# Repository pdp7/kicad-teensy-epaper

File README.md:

# E-Paper Badge with Teensy LC designed in KiCad
E-Paper badge designed in [KiCad](http://kicad.org/) to connect [Pervasive Displays 2.15" E-Paper](http://www.digikey.com/product-detail/en/pervasive-displays/E2215CS062/E2215CS062-ND/5975949) to [Teensy LC](http://store.oshpark.com/products/teensy-lc). _([Teensy 3.2](https://oshpark.com/teensy) is also compatible)._  Based [Teensy E-Paper Shield](https://blog.oshpark.com/2016/08/27/teensy-e-paper-shield/) by [Jarek Lupinski](https://hackaday.io/Jarek) in EAGLE.

## OSH Park shared project
* [KiCad Teensy E-Paper Badge](https://oshpark.com/shared_projects/VzRNemk1)

## KiCad PCB design files
* repo: [kicad-teensy-epaper](https://github.com/pdp7/kicad-teensy-epaper/)
* commit: [add JST connector for lipo battery [abcafec]](https://github.com/pdp7/kicad-teensy-epaper/commit/abcafeccad423acb4cc5d59347c79b58a7b5082b)
* requires KiCad library [wickerlib](https://github.com/wickerbox/wickerlib) by [Jenner Hanni](http://jennerhanni.net/) of [Wickerbox Electronics](http://wickerbox.net/) for the 34-position FPC connector that the e-paper display plugs into:
  * [CONN-HEADER-FH34SRJ-34S-0.5SH.kicad_mod](https://github.com/wickerbox/wickerlib/blob/master/libraries/Wickerlib.pretty/CONN-HEADER-FH34SRJ-34S-0.5SH.kicad_mod)

## Bill of Materials (BoM)
* [OSH Stencils](https://www.oshstencils.com/#projects/83952319ea2abc27d46ef9cab843063dbfd85e58): stainless steel stencil
* [Teensy LC](http://store.oshpark.com/products/teensy-lc) sold by OSH Park. Designed and manufactured by [PJRC](https://www.pjrc.com/teensy/teensyLC.html).
  * _[Teensy 3.2](https://oshpark.com/teensy) is also compatible but more expensive_
* [Pervasive Displays 2.15" e-paper with ITC](http://www.pervasivedisplays.com/products/215)
  * Mfg part number: E2215CS062
  * Digi-Key: [E2215CS062-ND](http://www.digikey.com/product-detail/en/pervasive-displays/E2215CS062/E2215CS062-ND/5975949)
  * Datasheet: [2.15" TFT EPD Panel (E2215CS062)](http://www.pervasivedisplays.com/LiteratureRetrieve.aspx?ID=232067)
  * App note: [2.15" Aurora_Mb Application Note](http://www.pervasivedisplays.com/LiteratureRetrieve.aspx?ID=232068)
* [Hirose FH34SRJ-34S-0.5SH FPC connector](https://www.digikey.com/short/3hv1q0)
  * Mfg part number: FH34SRJ-34S-0.5SH(99)
  * Digi-Key: [H124726CT-ND](https://www.digikey.com/short/3hv1q0)
  * Datasheet: [FH34(S) Series Datasheet](https://www.hirose.com/product/en/download_file/key_name/FH34SRJ/category/Catalog/doc_file_id/31646/?file_category_id=4&item_id=27&is_series=1)
* [JST connector for LiPo battery](https://www.digikey.com/short/312bmm)
  * Mfg part number: S2B-PH-SM4-TB(LF)(SN)
  * Digikey: [455-1749-1-ND](https://www.digikey.com/short/312bmm) _(CONN HEADER PH SIDE 2POS 2MM SMD)_
  * Datasheet: [JST PH connector](http://www.jst-mfg.com/product/pdf/eng/ePH.pdf)  
* Teensy headers
  * Digikey: [S7012-ND](https://www.digikey.com/short/3db830) _(CONN HEADER FEMALE 14POS.1" TIN)_
  * optional as Teensy can be soldered directly to PCB
* Capacitor 1uF 0805 _(quantity 9)_
  * Digi-Key: [1276-1066-1-ND](https://www.digikey.com/short/3db8tm) _(CAP CER 1UF 25V X7R 0805)_
  * Reference: C1 C3 C4 C5 C6 C7 C8 C9 C10
  * _Note: it is cheaper to purhcase qty 10_
* Capacitor 2.2uF 0805
  * Digi-Key: [1276-2953-1-ND](https://www.digikey.com/short/3db8tp) _(CAP CER 2.2UF 25V X7R 0805)_
  * Reference: C2
* Inductor 47uH
  * Digi-Key: [732-7252-1-ND](https://www.digikey.com/short/3db8tq) _(FIXED IND 47UH 800MA 521 MOHM)_
  * Reference: L1
* Mosfet N-Ch SOT23
  * Digi-Key: [785-1012-1-ND](https://www.digikey.com/short/3db8t8) _(MOSFET N-CH 30V 3.8A SOT23)_
  * Reference: Q1
* Resistor 2.2 Ohm 0805
  * Digi-Key: [311-2.20CRCT-ND](https://www.digikey.com/short/3db8tz) _(RES SMD 2.2 OHM 1% 1/8W 0805)_
  * Reference: R1
* Schotty diodes SOD123 _(quantity 3)_
  * Digi-Key: [MBR0530CT-ND](https://www.digikey.com/short/3db883) _(DIODE SCHOTTKY 30V 500MA SOD123)_
  * Reference: D1 D2 D3

### [Digi-Key shopping cart](http://www.digikey.com/short/312b57)

### Battery Power
* **WARNING: The trace between VIN and VUSB must be cut!**
  * [Demostration of cutting the trace](https://learn.adafruit.com/assets/28069) on Adafruit Learning System.
* **[Lithium Ion Polymer Battery - 3.7v 500mAh](https://www.adafruit.com/product/1578)** from Adafruit
  * capacity chosen for a good trade off between weight and power
  * TODO: measure how long board will run with different capacities.

## Source Code
* uses [EPD215](https://github.com/jarek319/EPD215) Arduino Library by Jarek Lupinski for his E-paper Teensy Shield
* requires pinout modification:
  * example: [bringahackmfba17-dorkbotpdx.ino](https://github.com/pdp7/kicad-teensy-epaper/blob/master/firmware/bringahackmfba17-dorkbotpdx/bringahackmfba17-dorkbotpdx.ino#L6)
  * `EPD215 epaper( 17, 16, 14, 15, 13, 11 );`
 * rotation hack in [`EPD215.cpp`](https://github.com/pdp7/EPD215/commit/f4e22660877759e53a3a83ed35c6e7a54616d285#diff-a3705673e6074c2678102896fd9fc17b)
   * text and graphics wil be upside down without this
   * [quick hack to set rotation](https://github.com/pdp7/EPD215/commit/f4e22660877759e53a3a83ed35c6e7a54616d285) based on [Adafruit documentation](https://learn.adafruit.com/adafruit-gfx-graphics-library/rotating-the-display): 
   * Landscape mode:
     * `_rotation = 1`
   * Portrait mode:
     * `_rotation = 2`
   * I don't use this for the examples program that just display bitmaps as I just flip the image before generating the byte array from the bitmap file

**TODO:** library should be modified to accept rotation parameter
  
## Photos
* [Google Photos gallery](https://goo.gl/photos/csZV9jxah2BSP6vG9)
* [images directory in github repo](https://github.com/pdp7/kicad-teensy-epaper/tree/master/images)

## Video
* [YouTube: *E-Paper Badge with Teensy LC designed in KiCad*](https://www.youtube.com/watch?v=AxnLgPFTEOA)

## Related: Jarek's ePaper Teensy shield
  * OSH Park shared project: [Teensy e-Paper shield](https://oshpark.com/shared_projects/3KynIVn6)
  * My repo of Jarek's design files: [TeensyEpaperShield](https://github.com/pdp7/TeensyEpaperShield)

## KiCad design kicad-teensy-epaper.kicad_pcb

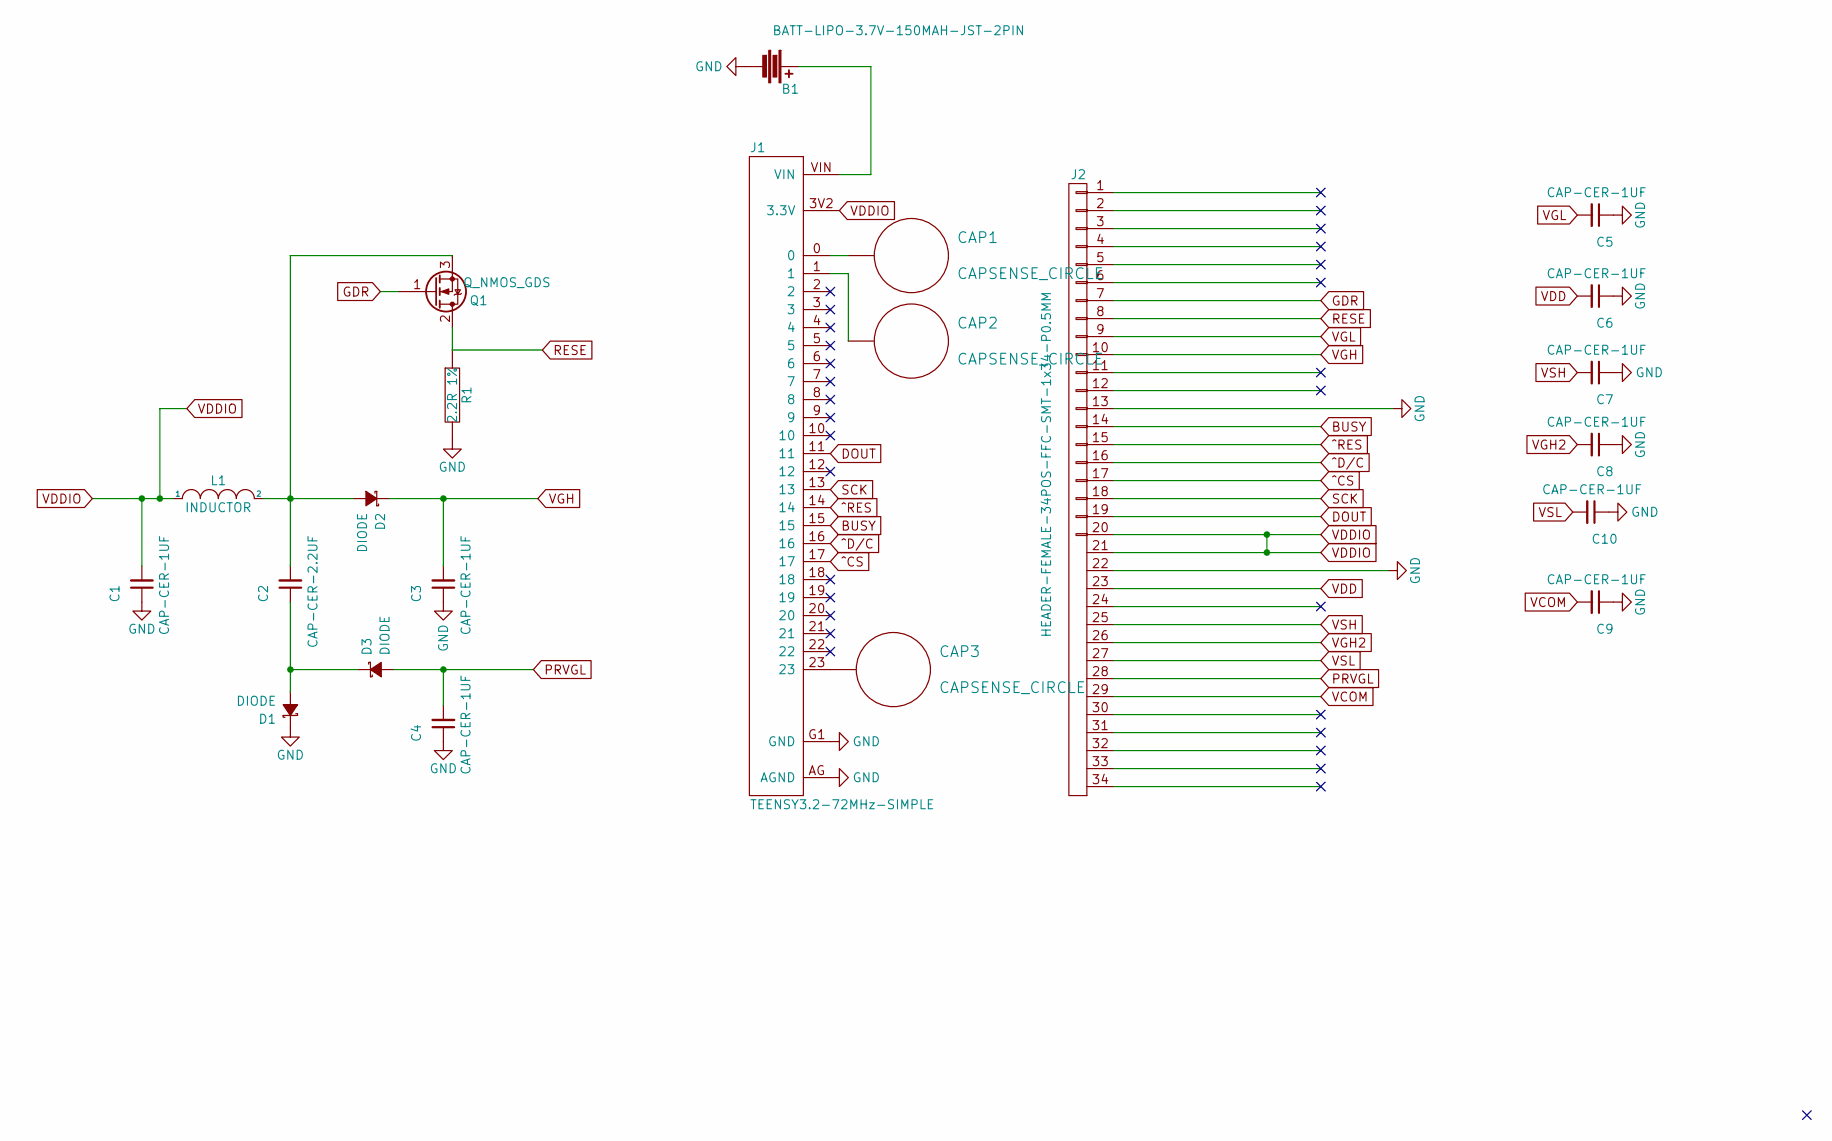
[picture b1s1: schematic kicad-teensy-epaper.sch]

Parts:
B1: BATT-LIPO-3.7V-150MAH-JST-2PIN; JST_PH_B2B-PH-SM4-TB_02x2.00mm_Straight
C1, C3, C4, C5, C6, C7, C8, C9, C10: CAP-CER-1UF; C_0805_HandSoldering
C2: CAP-CER-2.2UF; C_0805_HandSoldering
CAP1, CAP2, CAP3: CAPSENSE_CIRCLE; CAPSENSE-CIRCLE-D10MM
D1, D2, D3: DIODE; SOD-123
J1: TEENSY3.2-72MHz-SIMPLE; TEENSY-3.2-SILK-SIMPLE
J2: HEADER-FEMALE-34POS-FFC-SMT-1x34-P0.5MM; CONN-HEADER-FH34SRJ-34S-0.5SH
L1: INDUCTOR; Inductor_1212
Q1: Q_NMOS_GDS; SOT-23_Handsoldering
R1: 2.2R 1%; R_0805_HandSoldering

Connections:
BUSY: J1.15, J2.14
DOUT: J1.11, J2.19
GDR: J2.7, Q1.1 (G)
GND: B1.2, C1.1, C3.1, C4.1, C5.1, C6.1, C7.1, C8.1, C9.1, C10.1, D1.1 (K), J1.AG (AGND), J1.G1 (GND), J2.13, J2.22, R1.2
unnamed: B1.1, J1.VIN
unnamed: C2.1, D1.2 (A), D3.1 (K)
unnamed: C2.2, D2.2 (A), L1.2, Q1.3 (S)
unnamed: CAP1.1, J1.0
unnamed: CAP2.1, J1.1
unnamed 9: CAP3.1, J1.23; also elsewhere on the board
PRVGL: C4.2, D3.2 (A), J2.28
RESE: J2.8, Q1.2 (D), R1.1
SCK: J1.13, J2.18
VCOM: C9.2, J2.29
VDD: C6.2, J2.23
VDDIO: C1.2, J1.3V2 (3.3V), J2.20, J2.21, L1.1
VGH: C3.2, D2.1 (K), J2.10
VGH2: C8.2, J2.26
VGL: C5.2, J2.9
VSH: C7.2, J2.25
VSL: C10.2, J2.27
^CS: J1.17, J2.17
^D/C: J1.16, J2.16
^RES: J1.14, J2.15

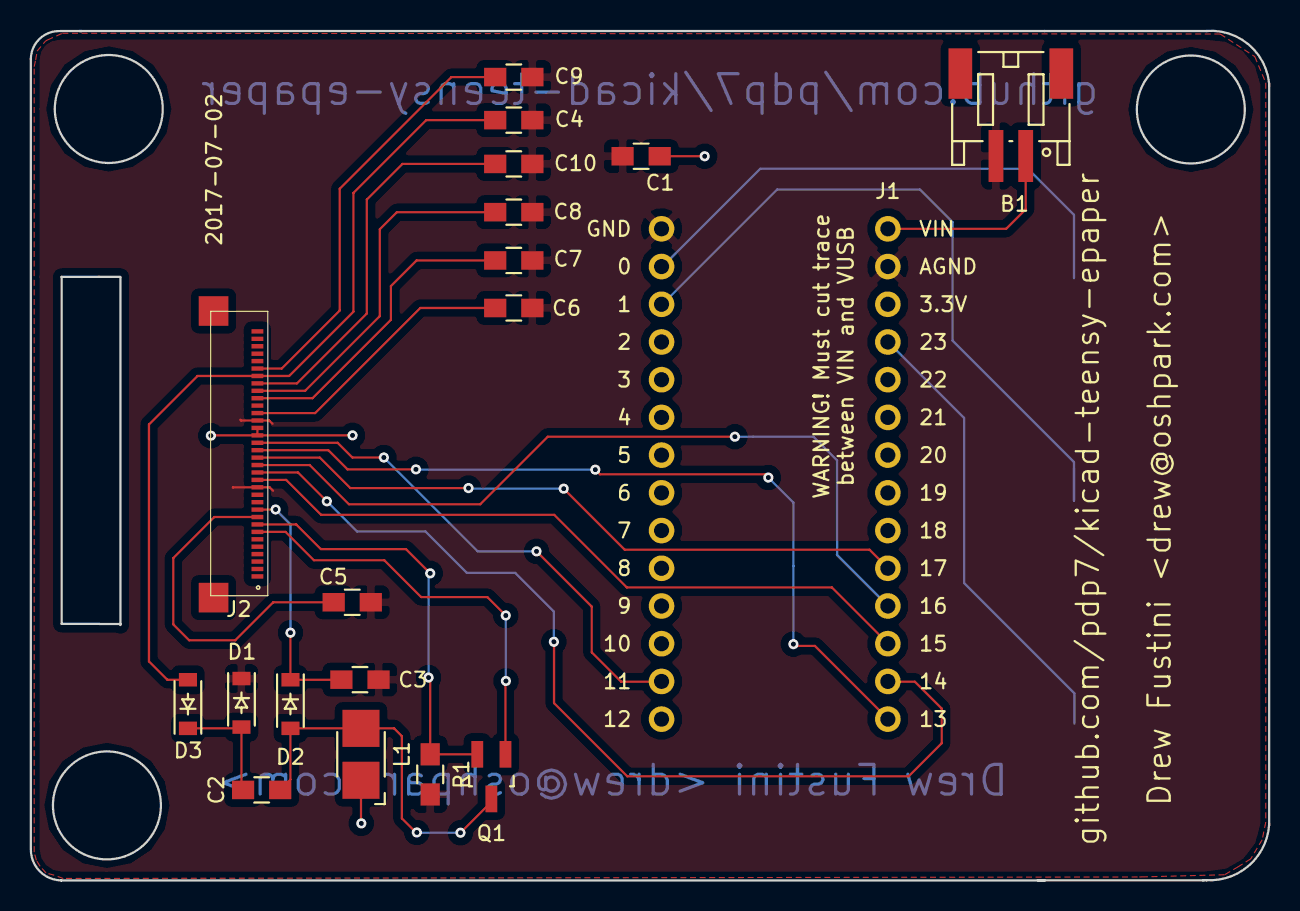
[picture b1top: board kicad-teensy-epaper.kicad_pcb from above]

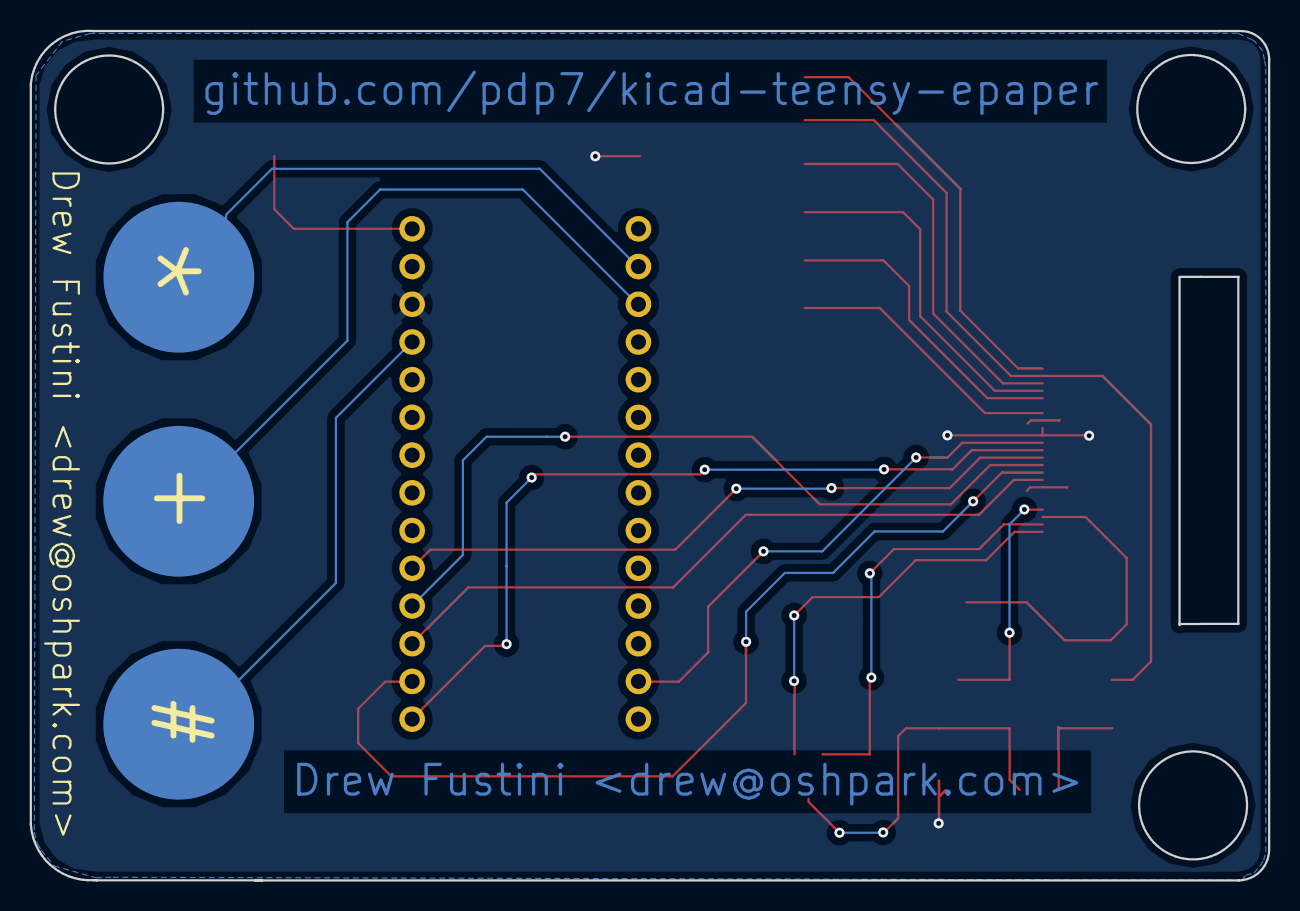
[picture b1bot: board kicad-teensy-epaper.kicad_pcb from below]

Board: 2 copper layers, 83.4 x 57.2 mm, 22 parts (3 on the bottom side), 24 nets.

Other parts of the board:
A: CAPSENSE_CIRCLE; CAPSENSE-CIRCLE-D10MM

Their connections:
unnamed 9: A.1; also elsewhere on the board

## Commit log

2017-01-06 Add initial Kicad project files
2017-01-07 create small board to test footprint
2017-01-14 start the schematic and layout over
2017-02-03 finish redrawing the EAGLE schematic in KiCad
    TODO: make sure the correct parts are used for passives and mosfet
2017-02-04 first attempt at layout, 1 air wire remains
2017-03-29 order new version
2017-03-29 add gerbers
2017-04-07 add images
2017-04-07 add example code
2017-04-07 add photos of digi-key BoM
2017-04-07 add small image of BoM
2017-04-07 add kicad screenshots
2017-04-08 make ground pads bigger on FPC 34-pos connector
2017-04-08 Revert "make ground pads bigger on FPC 34-pos connector"
    This reverts commit 6fa3f84300bf43afcb1b2505809670445bb03ed8.
    This commit was intended for the 'badge' branch
2017-04-14 added slot and rerouted traces
2017-04-22 add photo of e-paper badge
2017-04-26 redesigned for smaller size and cap touch
2017-04-26 label cap touch buttons
2017-04-26 update schematic
2017-04-26 move C5 to avoid connector
2017-04-26 update layout
2017-05-04 Reworked layout for aesthetics
    OSH Park order m5ay7bby on May 4th, 2017.
2017-06-02 update README for new badge
2017-06-02 update preview images
2017-06-02 update small preview images
2017-06-02 add photos of epaper badge
2017-06-02 Create oshpark_shared_project.md
    back up content of shared project:
    https://oshpark.com/shared_projects/1CiimZcf
2017-07-03 Set pad soldermask clearance to 0
    The display fine pitch connector footprint
    does not have solder mask between the pads.
    Chris Boros advised I could have solder mask
    between the pads by setting the clearance to 0.
2017-07-03 add JST connector for lipo battery
2017-08-23 update board preview and digi-key bom images
2017-08-23 update digi-key bom graphic
2017-08-23 make the preview images smaller
2017-08-28 update images and code
2017-08-28 add info on LCD Assistant utiltiy from: http://en.radzio.dxp.pl/bitmap_converter/
2017-08-31 create git submodule for EPD215 library
2017-08-31 add submodule for FancyEPD
2017-08-31 remove uneeded script
2017-08-31 add photos of grayscale images with FancyEPD
2017-08-31 update gerbers for most recent layout
2017-08-31 add images of the front and back of the badge
2017-09-07 add photos osh stencils shared project
2017-09-07 Add setRotation() option
2017-09-07 dd setRotation() option
2017-09-07 update to latest pdp7/EPD215 master branch
2017-09-12 update EPD215 submodule
2017-10-03 update OHS17 FancyEPD 4-bit images
2021-11-08 Update README.md
    https://forum.kicad.info/t/warning-avoid-all-links-to-kicad-pcb-org-use-kicad-org/31521
